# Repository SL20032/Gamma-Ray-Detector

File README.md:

# Gamma Ray Detector

## Basic informations
Solid State gamma Ray detector based around PiN Diodeds (BPW34) as detection element and discreate transistor (BC549) as signal preamplifire (based on design published in Elektor magazine 06 - 2011). To increse detection rate of radiation while keeping good sensytivity espesialy for lower energy particles, device uses spit head approch - detection diodes are wired intu multiple detection heads (preamplifires) from witch output signal is then integrated and digitalized using compartor(LM393).

## Specs:
- Input voltage: 9V
- Data Procesing MCU: Attiny402 or pin compatible (so8 to dip8 adapter is nesesery in current board revision) 
## Theory of operation
TBA
## Digital signal procesing
Digital procesing is based on Attine402. Depending on the selected configuration data could be accese by a user e.g. through a COM port connection or an attached alfanumeric display. this solution supports counting all radioation events since device power up or counter reset (push button on the board) as well as a estimeted CPM (counts per minute). MCU firmware coming soon.
## Comparator circut calibration
To asure proper operation of detector's digital side nessesery is proper seting of reference voltage for comparator the easiest way to do this is:
- connect osciloscope to non inverting input of comparator (pin 3 on IC3) and to output of the same comparator (pin 1 on IC3)
- put the detector in area with minimal radiation (in most cases it is enought not to be in close procimty to ane designated sorce)
- dial the potenciometer (R19) until optput of a Comparator (IC3) stays low - set refernece voltage above a noice floor of a system
## Detection resoults

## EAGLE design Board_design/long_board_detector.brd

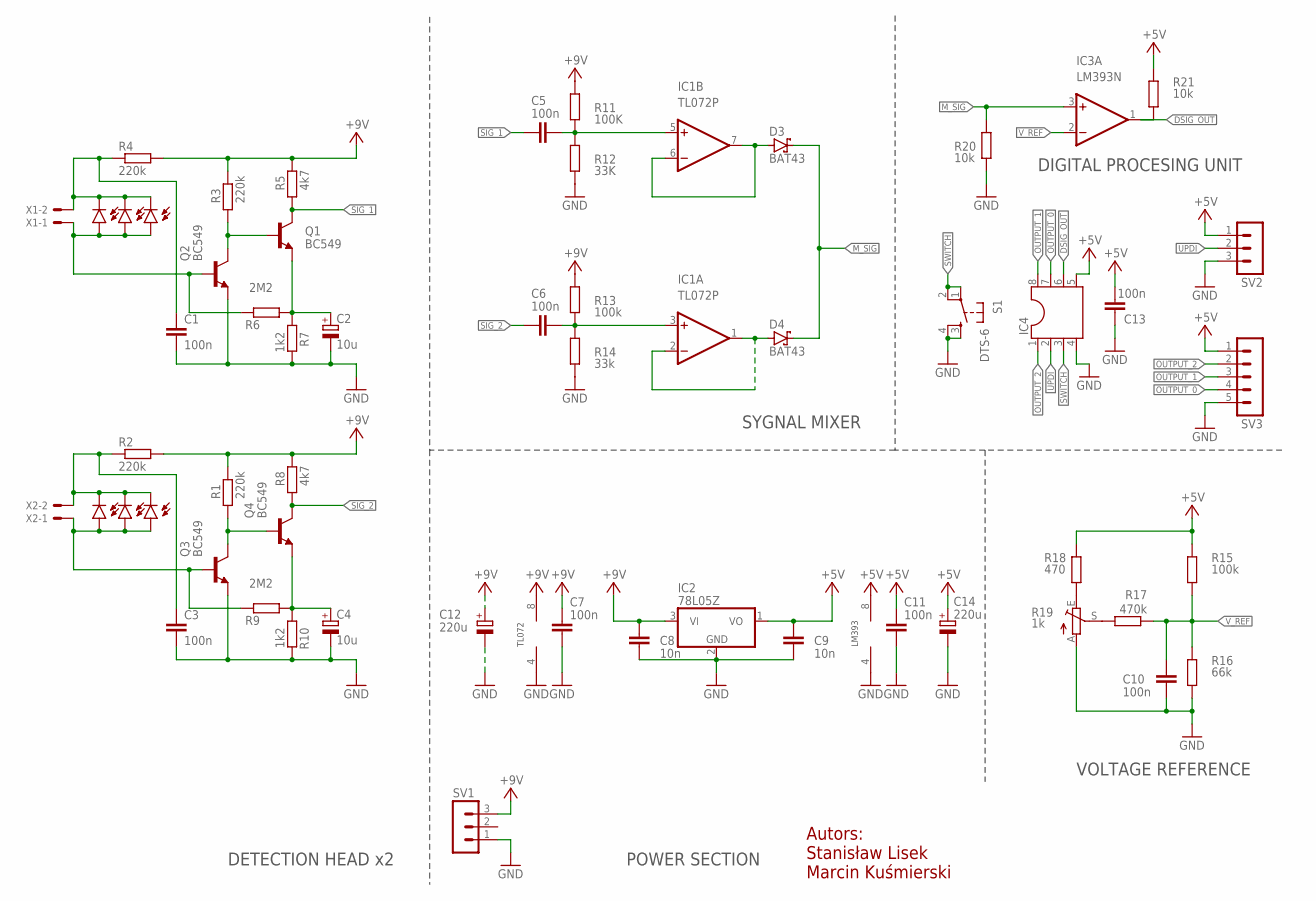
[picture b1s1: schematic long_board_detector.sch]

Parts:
C1, C3, C5, C6, C7, C10, C11, C13: 100n; C050-025X075
C2, C4: 10u; E2,5-6E
C8, C9: 10n; C050-025X075
C12, C14: 220u; E2,5-6E
D1, D2, D5, D6, D7, D8: BPW32
D3, D4: BAT43; DO35-10
IC1: TL072P; DIL08
IC2: 78L05Z; TO92
IC3: LM393N; DIL08
IC4: DIL8S; SOCKET-08
Q1, Q2, Q3, Q4: BC549; TO92-EBC
R1, R2, R3, R4: 220k; 0204/7
R5, R8: 4k7; 0204/7
R6, R9: 2M2; 0204/7
R7, R10: 1k2; 0204/7
R11: 100K; 0204/7
R12: 33K; 0204/7
R13, R15: 100k; 0204/7
R14: 33k; 0204/7
R16: 66k; 0204/7
R17: 470k; 0204/7
R18: 470; 0204/7
R19: 1k; CA6V
R20, R21: 10k; 0204/7
S1: DTS-6
SV1, SV2: MA03-1
SV3: MA05-1
X1, X2: 22-23-2021

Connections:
+3V3: C9.1, C11.2, C13.2, C14.+, IC2.1 (VO), IC3.8 (V+), IC4.5, R15.1, R18.2, R21.1, SV2.1, SV3.1
+5V: C7.2, C8.1, C12.+, IC1.8 (V+), IC2.3 (VI), R1.2, R2.2, R3.2, R4.2, R5.2, R8.2, R11.1, R13.1, SV1.3
DSIG_OUT: IC3.1 (OUT), IC4.6, R21.2
GND: C1.2, C2.-, C3.2, C4.-, C7.1, C8.2, C9.2, C10.2, C11.1, C12.-, C13.1, C14.-, IC1.4 (V-), IC2.2 (GND), IC3.4 (V-), IC4.4, Q2.E, Q3.E, R7.2, R10.2, R12.2, R14.2, R16.2, R19.A, R20.2, S1.3, S1.4, SV1.1, SV2.3, SV3.5
M_SIG: D3.C, D4.C, IC3.3 (+IN), R20.1
unnamed: D6.A, D7.A, D8.A, Q3.B, R9.2, X2.1
unnamed: C5.2, IC1.5 (+IN), R11.2, R12.1
unnamed: Q1.B, Q2.C, R3.1
unnamed: D1.A, D2.A, D5.A, Q2.B, R6.2, X1.1
unnamed: D4.A, IC1.1 (OUT), IC1.2 (-IN)
unnamed: D3.A, IC1.6 (-IN), IC1.7 (OUT)
unnamed: C2.+, Q1.E, R6.1, R7.1
unnamed: C6.2, IC1.3 (+IN), R13.2, R14.1
unnamed: C1.1, D1.K (C), D2.K (C), D5.K (C), R4.1, X1.2
unnamed: C3.1, D6.K (C), D7.K (C), D8.K (C), R2.1, X2.2
unnamed: Q3.C, Q4.B, R1.1
unnamed: C4.+, Q4.E, R9.1, R10.1
unnamed: R17.1, R19.S
unnamed: R18.1, R19.E
OUTPUT_0: IC4.7, SV3.4
OUTPUT_1: IC4.8, SV3.3
OUTPUT_2: IC4.1, SV3.2
SIG_1: C5.1, Q1.C, R5.1
SIG_2: C6.1, Q4.C, R8.1
SWITCH: IC4.3, S1.1, S1.2
UPDI: IC4.2, SV2.2
V_REF: C10.1, IC3.2 (-IN), R15.2, R16.1, R17.2

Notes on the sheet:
TL072
DETECTION HEAD x2
POWER SECTION
VOLTAGE REFERENCE
SYGNAL MIXER
DIGITAL PROCESING UNIT
LM393
Autors: Stanisław Lisek Marcin Kuśmierski

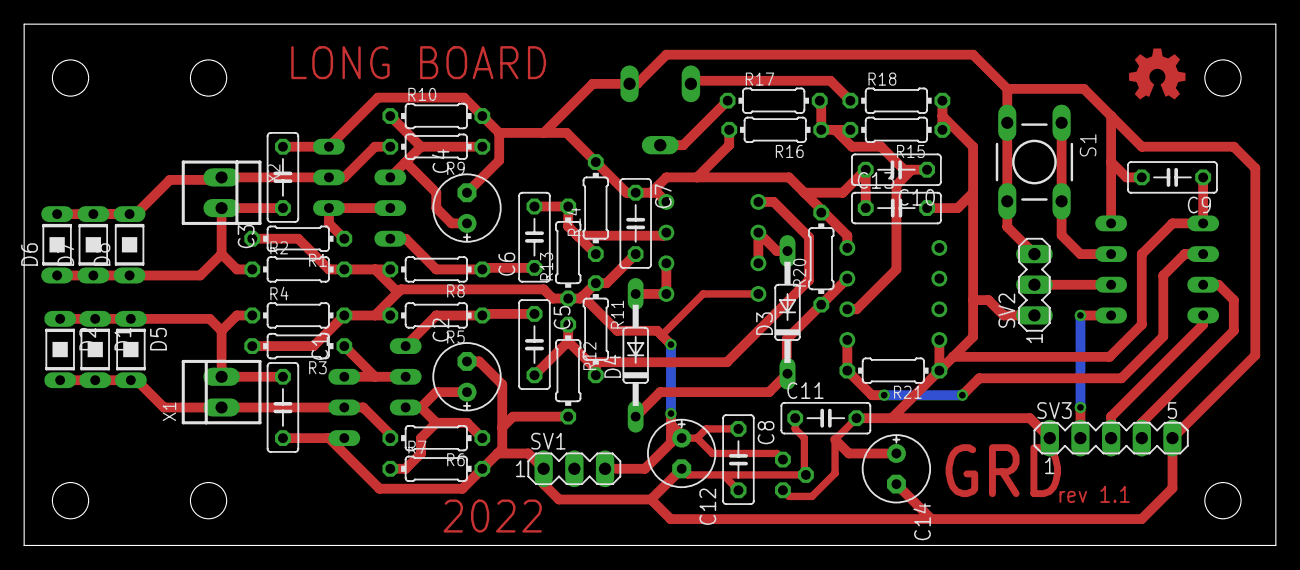
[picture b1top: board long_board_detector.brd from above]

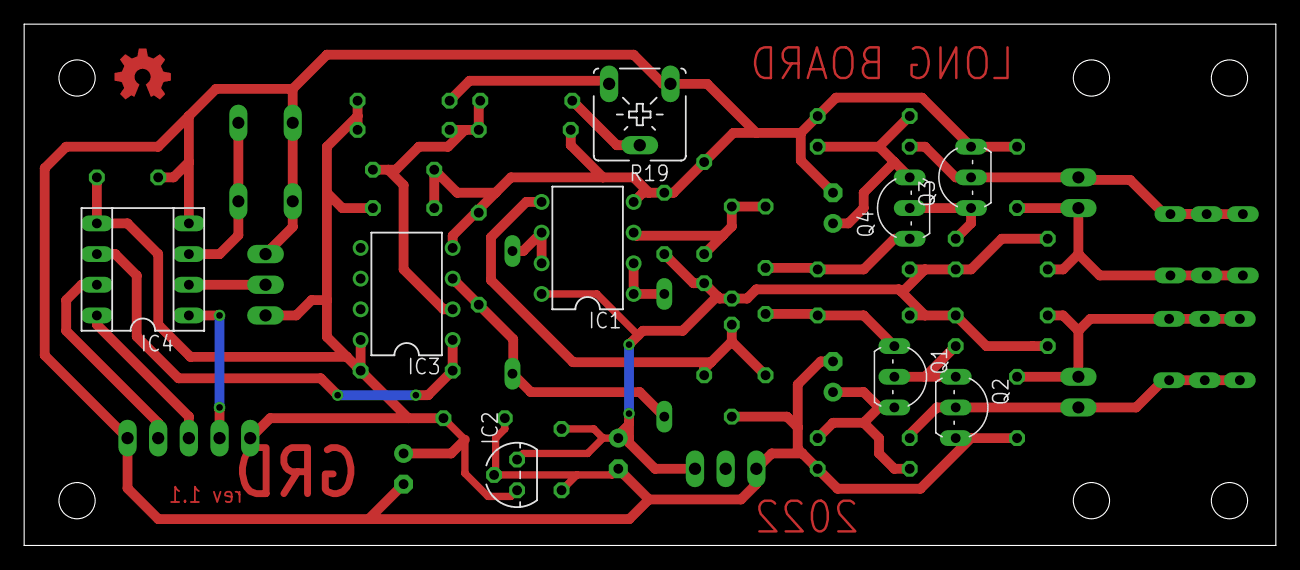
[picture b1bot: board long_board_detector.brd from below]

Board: 2 copper layers, 103.6 x 43.2 mm, 57 parts (9 on the bottom side), 27 nets.

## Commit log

2022-09-15 Add PCB design
2022-09-15 Readme update
2022-09-15 Create license
2022-09-15 Rename license to LICENSE
2022-09-15 Readme and brd design update
2022-09-30 UART MCU Firmware
2022-10-04 MCU Firmware: Counter and CPM implementation
